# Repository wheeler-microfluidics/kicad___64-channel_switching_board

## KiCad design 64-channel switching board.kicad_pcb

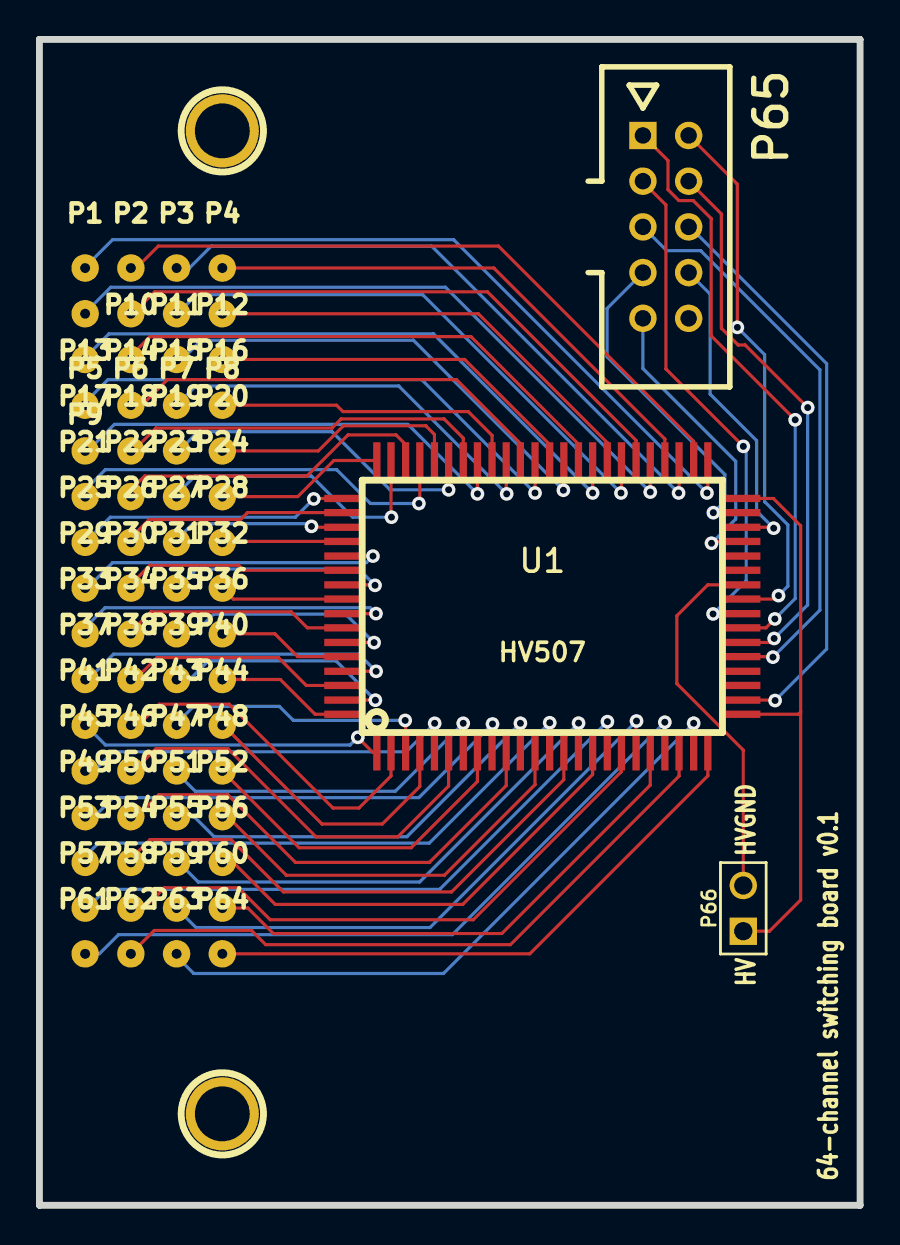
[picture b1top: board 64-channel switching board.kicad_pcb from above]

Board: 2 copper layers, 45.6 x 64.8 mm, 69 parts (0 on the bottom side), 75 nets.

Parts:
H2: H2; 1pin
H3: H3; 1pin
P1, P2, P3, P4, P5, P6, P7, P8, P9, P10, P11, P12, P13, P14, P15, P16, P17, P18, P19, P20, P21, P22, P23, P24, P25, P26, P27, P28, P29, P30, P31, P32, P33, P34, P35, P36, P37, P38, P39, P40, P41, P42, P43, P44, P45, P46, P47, P48, P49, P50, P51, P52, P53, P54, P55, P56, P57, P58, P59, P60, P61, P62, P63, P64: CONN_01X01; pogo_pin
P65: CONN_01X10; he10-10d
P66: CONN_01X02; PIN_ARRAY_2X1
U1: HV507; PQFP80

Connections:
+5V: P65.1, U1.31
BL: P65.5, U1.29
CLK: P65.9, U1.37
DIOA: P65.6, U1.26
DIOB: P65.7, U1.39
DIR: P65.3, U1.32
GND: P65.2, U1.33
LE: P65.8, U1.38
unnamed: P1.1, U1.41
unnamed: P2.1, U1.42
unnamed: P3.1, U1.43
unnamed: P4.1, U1.44
unnamed: P5.1, U1.45
unnamed: P6.1, U1.46
unnamed: P7.1, U1.47
unnamed: P8.1, U1.48
unnamed: P9.1, U1.49
unnamed: P10.1, U1.50
unnamed: P11.1, U1.51
unnamed: P12.1, U1.52
unnamed: P13.1, U1.53
unnamed: P14.1, U1.54
unnamed: P15.1, U1.55
unnamed: P16.1, U1.56
unnamed: P17.1, U1.57
unnamed: P18.1, U1.58
unnamed: P19.1, U1.59
unnamed: P20.1, U1.60
unnamed: P21.1, U1.61
unnamed: P22.1, U1.62
unnamed: P23.1, U1.63
unnamed: P24.1, U1.64
unnamed: P25.1, U1.65
unnamed: P26.1, U1.66
unnamed: P27.1, U1.67
unnamed: P28.1, U1.68
unnamed: P29.1, U1.69
unnamed: P30.1, U1.70
unnamed: P31.1, U1.71
unnamed: P32.1, U1.72
unnamed: P33.1, U1.73
unnamed: P34.1, U1.74
unnamed: P35.1, U1.75
unnamed: P36.1, U1.76
unnamed: P37.1, U1.77
unnamed: P38.1, U1.78
unnamed: P39.1, U1.79
unnamed: P40.1, U1.80
unnamed: P41.1, U1.1
unnamed: P42.1, U1.2
unnamed: P43.1, U1.3
unnamed: P44.1, U1.4
unnamed: P45.1, U1.5
unnamed: P46.1, U1.6
unnamed: P47.1, U1.7
unnamed: P48.1, U1.8
unnamed: P49.1, U1.9
unnamed: P50.1, U1.10
unnamed: P51.1, U1.11
unnamed: P52.1, U1.12
unnamed: P53.1, U1.13
unnamed: P54.1, U1.14
unnamed: P55.1, U1.15
unnamed: P56.1, U1.16
unnamed: P57.1, U1.17
unnamed: P58.1, U1.18
unnamed: P59.1, U1.19
unnamed: P60.1, U1.20
unnamed: P61.1, U1.21
unnamed: P62.1, U1.22
unnamed: P63.1, U1.23
unnamed: P64.1, U1.24
unnamed: P66.1, U1.25, U1.40
unnamed: P66.2, U1.34
POL: P65.4, U1.30

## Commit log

2015-09-24 Add labels to header pins
2016-01-20 Update .gitmodules file to point to github
2017-07-13 added appveyor.yml
2017-07-14 AppVeyor Configuration Updated
2017-07-18 AppVeyor Update: "a4e909ac7a44d2708564d46a9b978b95c8367686"
2017-07-19 AppVeyor Update: "d5d159050eac48ab9123f383fe8e949476d7f60f"
2017-07-20 AppVeyor Update: "35852f667457a927c170bb71278740b12d7a8f75"
